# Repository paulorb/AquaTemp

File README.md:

# AquaTemp
Peltier controller hardware

For more information check the Wiki tab

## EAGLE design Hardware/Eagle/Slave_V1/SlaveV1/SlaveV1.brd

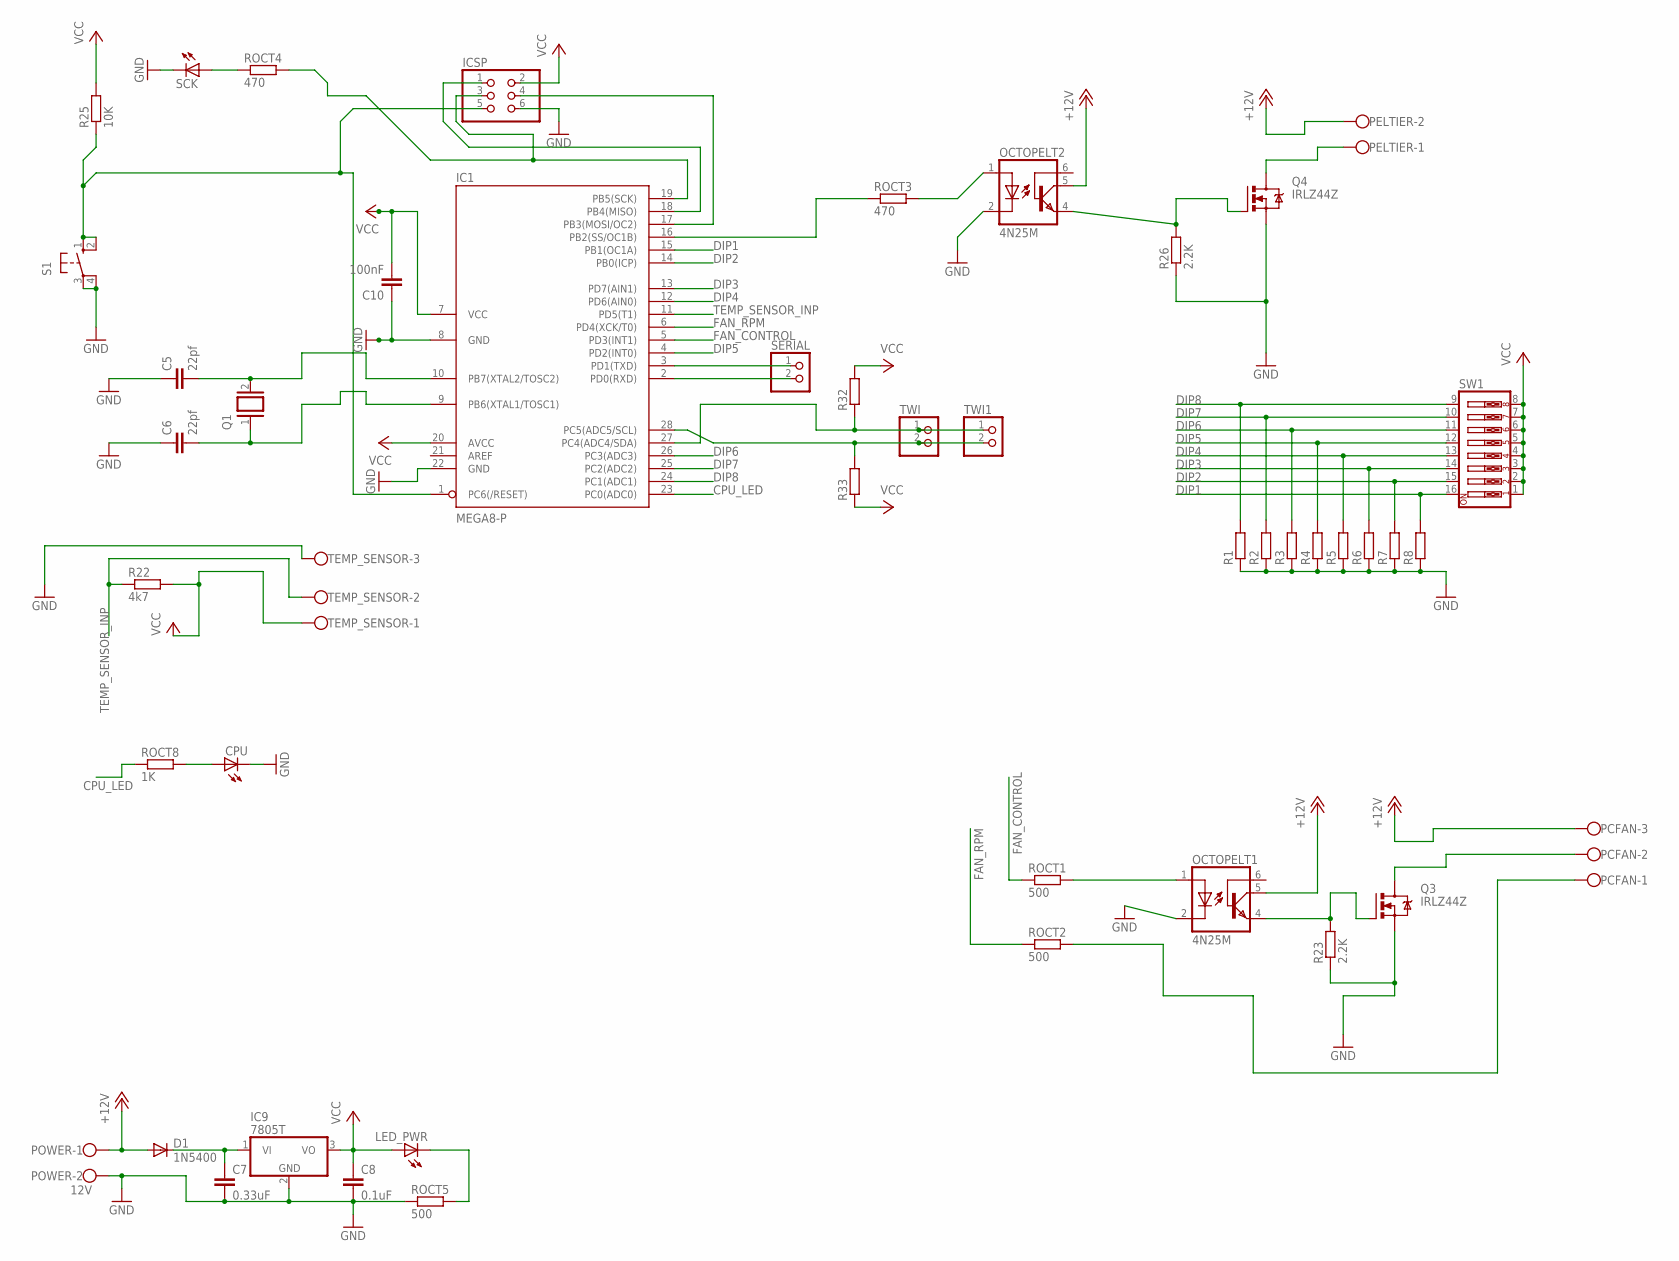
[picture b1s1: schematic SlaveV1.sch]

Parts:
C5, C6: 22pf; C2.5-3
C7: 0.33uF; C2.5-3
C8: 0.1uF; C2.5-3
C10: 100nF; C2.5-3
CPU: LED5MM
D1: 1N5400; DO201-15
IC1: MEGA8-P; DIL28-3
IC9: 7805T; TO220H
ICSP: PINHD-2X3; 2X03
LED_PWR: LED5MM
OCTOPELT1, OCTOPELT2: 4N25M; DIL06
PCFAN: W237-103
PELTIER: W237-102
POWER: 12V; W237-102
Q1: XTAL; Q
Q3, Q4: IRLZ44Z; TO220BH
R1, R2, R3, R4, R5, R6, R7, R8, R32, R33: R-EU_0207/10; 0207/10
R22: 4k7; 0204/7
R23, R26: 2.2K; 0204/7
R25: 10K; 0204/7
ROCT1, ROCT2, ROCT5: 500; 0204/7
ROCT3, ROCT4: 470; 0204/7
ROCT8: 1K; 0204/7
S1: 10-XX; B3F-10XX
SCK: LED5MM
SERIAL: PINHD-1X2/90; 1X02/90
SW1: SW_DIP-8; EDG-08
TEMP_SENSOR: W237-103
TWI, TWI1: PINHD-1X2/90; 1X02/90

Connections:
+12V: D1.A, OCTOPELT1.5 (COL), OCTOPELT2.5 (COL), PCFAN.3, PELTIER.2, POWER.1
CPU_LED: IC1.23 (PC0(ADC0)), ROCT8.1
DIP1: IC1.15 (PB1(OC1A)), R8.2, SW1.16
DIP2: IC1.14 (PB0(ICP)), R7.2, SW1.15
DIP3: IC1.13 (PD7(AIN1)), R6.2, SW1.14
DIP4: IC1.12 (PD6(AIN0)), R5.2, SW1.13
DIP5: IC1.4 (PD2(INT0)), R4.2, SW1.12
DIP6: IC1.26 (PC3(ADC3)), R3.2, SW1.11
DIP7: IC1.25 (PC2(ADC2)), R2.2, SW1.10
DIP8: IC1.24 (PC1(ADC1)), R1.2, SW1.9
FAN_CONTROL: IC1.5 (PD3(INT1)), ROCT1.1
FAN_RPM: IC1.6 (PD4(XCK/T0)), ROCT2.1
GND: C5.1, C6.1, C7.2, C8.2, C10.1, CPU.K (C), IC1.8 (GND), IC1.22 (GND), IC9.2 (GND), ICSP.6, OCTOPELT1.2 (C), OCTOPELT2.2 (C), POWER.2, Q3.S, Q4.S, R1.1, R2.1, R3.1, R4.1, R5.1, R6.1, R7.1, R8.1, R23.1, R26.1, ROCT5.1, S1.3, S1.4 (P1), SCK.K (C), TEMP_SENSOR.3
unnamed: IC1.3 (PD1(TXD)), SERIAL.1
unnamed: IC1.2 (PD0(RXD)), SERIAL.2
unnamed: C6.2, IC1.9 (PB6(XTAL1/TOSC1)), Q1.1
unnamed: C5.2, IC1.10 (PB7(XTAL2/TOSC2)), Q1.2
unnamed: OCTOPELT1.1 (A), ROCT1.2
unnamed: OCTOPELT1.4 (EMI), Q3.G, R23.2
unnamed: PCFAN.2, Q3.D
unnamed: PCFAN.1, ROCT2.2
unnamed: IC1.1 (PC6(/RESET)), ICSP.5, R25.1, S1.1 (S), S1.2 (S1)
unnamed: IC1.19 (PB5(SCK)), ICSP.3, ROCT4.2
unnamed: IC1.17 (PB3(MOSI/OC2)), ICSP.4
unnamed: IC1.18 (PB4(MISO)), ICSP.1
unnamed: OCTOPELT2.4 (EMI), Q4.G, R26.2
unnamed: PELTIER.1, Q4.D
unnamed: OCTOPELT2.1 (A), ROCT3.2
unnamed: IC1.16 (PB2(SS/OC1B)), ROCT3.1
unnamed: ROCT4.1, SCK.A
unnamed: C7.1, D1.C, IC9.1 (VI)
unnamed: LED_PWR.K (C), ROCT5.2
unnamed: CPU.A, ROCT8.2
SCL_PIN: IC1.28 (PC5(ADC5/SCL)), R33.2, TWI.2, TWI1.2
SDA_PIN: IC1.27 (PC4(ADC4/SDA)), R32.1, TWI.1, TWI1.1
TEMP_SENSOR_INP: IC1.11 (PD5(T1)), R22.1, TEMP_SENSOR.2
VCC: C8.1, C10.2, IC1.7 (VCC), IC1.20 (AVCC), IC9.3 (VO), ICSP.2, LED_PWR.A, R22.2, R25.2, R32.2, R33.1, SW1.1, SW1.2, SW1.3, SW1.4, SW1.5, SW1.6, SW1.7, SW1.8, TEMP_SENSOR.1

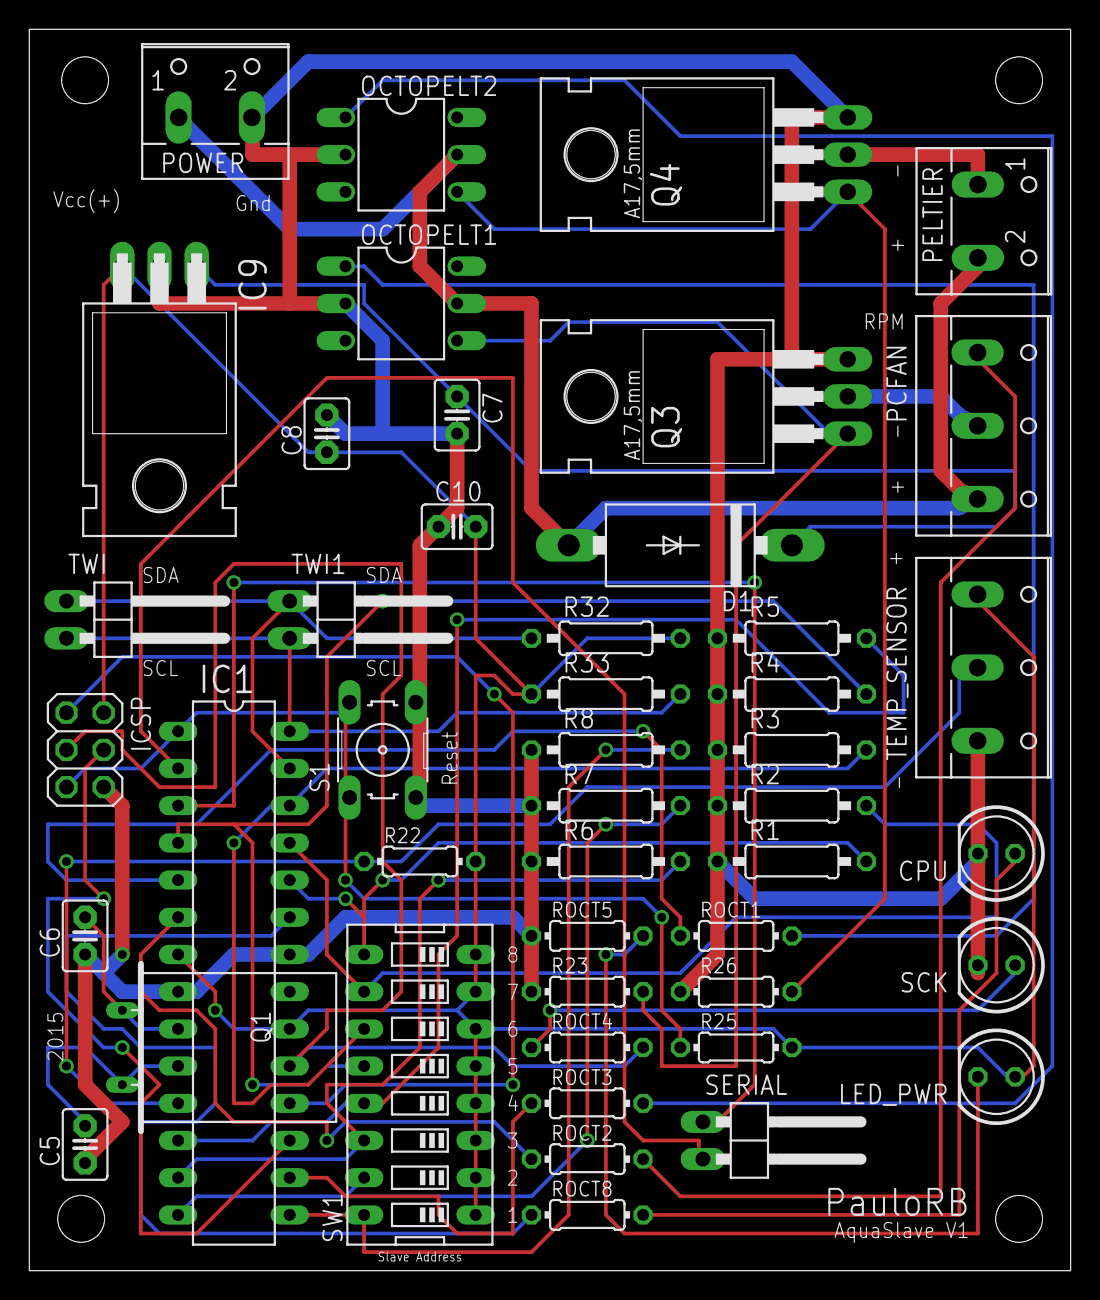
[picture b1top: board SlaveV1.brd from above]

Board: 2 copper layers, 71.1 x 84.8 mm, 46 parts (0 on the bottom side), 37 nets.

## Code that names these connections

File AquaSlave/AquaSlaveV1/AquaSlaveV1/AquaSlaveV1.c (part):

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

void PCFan_ON(){
	set_output(DDRD,PD3);
	output_high(PORTD,PD3);
}

void PCFan_OFF(){
	set_output(DDRD,PD3);
	output_low(PORTD,PD3);
}

void Peltier_ON(){
	set_output(DDRB,PB2);
	output_high(PORTB,PB2);
}

void Peltier_OFF(){
	set_output(DDRB,PB2);
	output_low(PORTB,PB2);
}


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// configuring T1 as external clock
// configuring timer T1
void  ConfigurePCFanWatch() {
	DDRD &= ~(1 << PD4);     // Clear the PB0 pin
	// PD0 is now an input
	PORTD |= (1 << PORTD4);   // turn On the Pull-up
	// PB0 is now an input with pull-up enabled

	TIMSK |= (1 << TOIE0);    // enable timer interrupt

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	// addresses us and wishes to write data to us

//	showByte(*receiveData);
	//cbi(PORTB, PB6);
	
	
	//STATE MACHINE START
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	// addresses us and wishes to read data from us

//	showByte(*transmitData);
	//cbi(PORTB, PB7);

	// copy the local buffer to the transmit buffer
	for(i=0; i<localBufferLength; i++)
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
